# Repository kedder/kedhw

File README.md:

# Various electronics projects for gliding

This is a collection of various electronics projects, generally supposed to be used in
glider cockpit. Each directory here is a separate hardware design. See README in each of
the subdirectories for more info.

## [FLARM Splitter](flarmsplit)

FLARM splitter allows to connect both vario and FLARM viewer to the FLARM device via the
standard RJ45 socket, providing RS232 data. 

## [FLARM - USB adapter](flarmusb)

FLARM to USB adapter allows to connect flarm device to the computer for firmware update.
It also creates a virtual COM device in the computer OS allowing data communication with
the FLARM device.

## [TTLINK](ttlink)

USB adapter that allows to connect various loggers and handheld computers to the
Openvario via the USB interface. Compatible hardware list includes "LXNAV Nano 4" and
"Naviter Oudie", and possibly others.

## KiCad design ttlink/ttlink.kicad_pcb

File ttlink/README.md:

# USB-TTL Adapter

Simple USB adapter to connect devices like LXNAV Nano loggers or Oudie. Even
though these devices have a standard micro/mini USB sockets, they do not talk
USB protocol with glider electonics. Instead, they use TTL signal. This adapter
uses CH340G chip to convert USB protocol to TTL.

## Schematics

Current schematics can be also downloaded in
[PDF format](drawings/ttlink.pdf?raw=true).

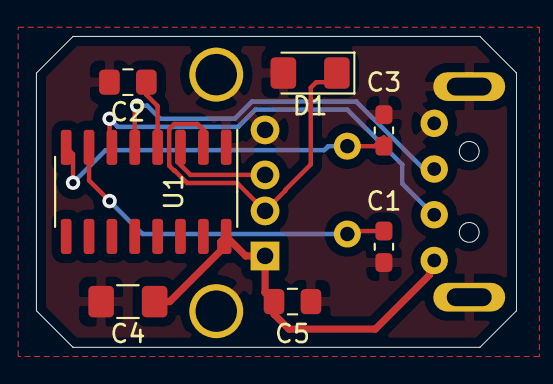
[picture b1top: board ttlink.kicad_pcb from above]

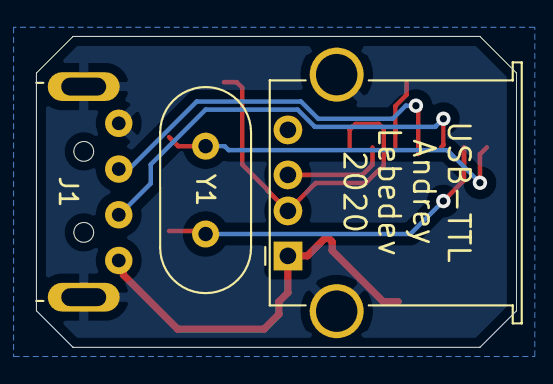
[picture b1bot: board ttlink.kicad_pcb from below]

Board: 2 copper layers, 26.7 x 17.3 mm, 10 parts (3 on the bottom side), 9 nets.

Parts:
C1, C3: 22pF; C_0603_1608Metric_Pad1.05x0.95mm_HandSolder
C2, C5: 0.1uF; C_0805_2012Metric_Pad1.15x1.40mm_HandSolder
C4: 10uF; C_1206_3216Metric_Pad1.42x1.75mm_HandSolder
D1: 1N4148; D_1206_3216Metric_Pad1.42x1.75mm_HandSolder
J1: USB; USB2_A_Plug_Horizontal
J2: TTL; USB_A_Stewart_SS-52100-001_Horizontal
U1: CH340G; SOIC-16_3.9x9.9mm_P1.27mm
Y1: 12MHz; Crystal_HC49-4H_Vertical

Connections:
+5V: C4.2, C5.2, J1.1, J2.1, U1.16
Earth: C1.2, C2.2, C3.2, C4.1, C5.1, D1.2, J1.4, J1.5, J2.4, J2.5, U1.1
unnamed: C1.1, U1.7, Y1.2
unnamed: C2.1, U1.4
unnamed: C3.1, U1.8, Y1.1
unnamed: D1.1, J2.2, U1.2
unnamed: J1.2, U1.6
unnamed: J1.3, U1.5
unnamed: J2.3, U1.3

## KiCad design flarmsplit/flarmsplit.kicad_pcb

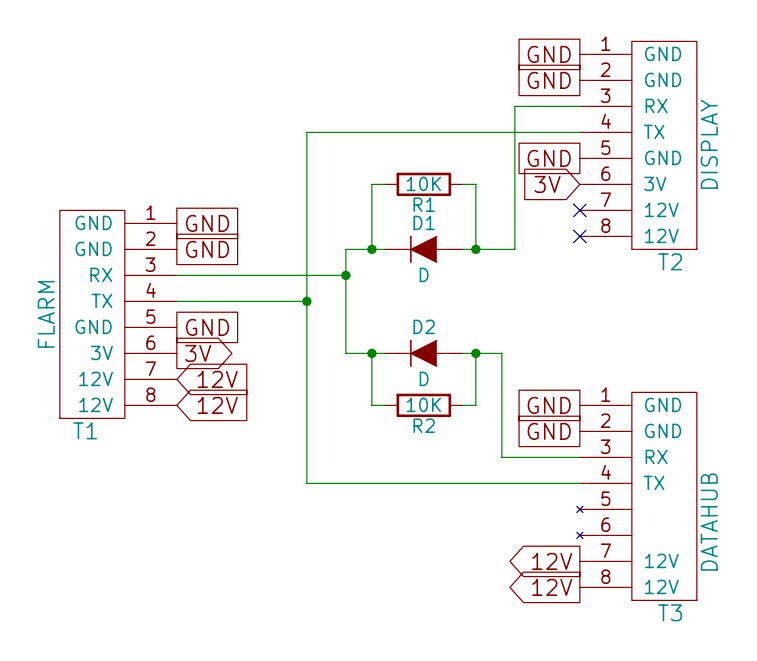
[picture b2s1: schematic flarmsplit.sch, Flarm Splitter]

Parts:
D1, D2: D; D_1206_3216Metric_Pad1.42x1.75mm_HandSolder
R1, R2: 10K; R_0805_2012Metric_Pad1.15x1.40mm_HandSolder
T1: FLARM; RJ45_SOCKET_SHLD
T2: DISPLAY; RJ45_SOCKET_SHLD
T3: DATAHUB; RJ45_SOCKET_SHLD

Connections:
3V: T1.6 (3V), T2.6 (3V)
12V: T1.7 (12V), T1.8 (12V), T3.7 (12V), T3.8 (12V)
GND: T1.1 (GND), T1.2 (GND), T1.5 (GND), T2.1 (GND), T2.2 (GND), T2.5 (GND), T3.1 (GND), T3.2 (GND)
unnamed: D1.1 (K), D2.1 (K), R1.2, R2.2, T1.3 (RX)
unnamed: D1.2 (A), R1.1, T2.3 (RX)
unnamed: D2.2 (A), R2.1, T3.3 (RX)
unnamed: T1.4 (TX), T2.4 (TX), T3.4 (TX)

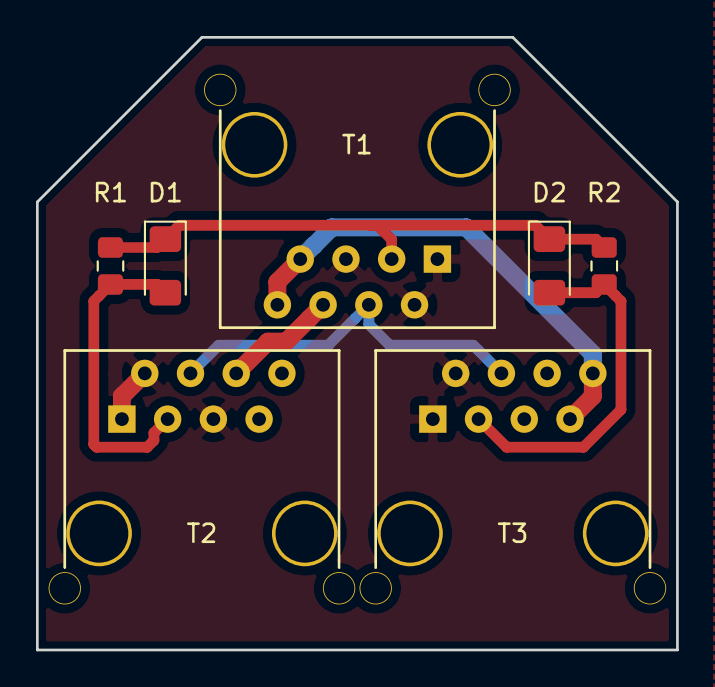
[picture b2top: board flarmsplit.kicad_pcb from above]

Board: 2 copper layers, 35.6 x 34.0 mm, 7 parts (0 on the bottom side), 7 nets.

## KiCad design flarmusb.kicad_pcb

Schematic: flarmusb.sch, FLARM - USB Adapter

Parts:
C1, C2: 22pF; C_0603_1608Metric
C3, C4, C5, C6, C7, C8: 100nF; C_0805_2012Metric
C9: 1uF; C_0805_2012Metric
C10: 47uF; C_0805_2012Metric
D1: SS14; D_SMA
D2: GREEN; LED_0603_1608Metric
D3: RED; LED_0603_1608Metric
J1: USB_B_Micro; USB_Micro
J2: Barrel_Jack_Switch; DC002
J3: RJ45_Shielded; RJ45_SOCKET_SHLD
R1, R2: 520R; R_0805_2012Metric
U1: LM3940-3.3; SOT-223-3_TabPin2
U2: CH340G; SOIC-16_3.9x9.9mm_P1.27mm
U3: MAX3232; SOIC-16_3.9x9.9mm_P1.27mm
Y1: 12M; Crystal_HC49-4H_Vertical

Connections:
3V3: C3.1, C5.2, C7.1, C10.2, R1.1, R2.1, U1.3, U2.4, U2.16, U3.16
/5V: C9.2, J1.1, U1.1
/12V: D1.1 (K), J3.7, J3.8
/12VR: D1.2 (A), J2.1
/RS232_RX: J3.4, U3.13
/RS232_TX: J3.3, U3.14
/TTL_RX: D2.1, U2.3, U3.12
/TTL_TX: D3.1, U2.2, U3.11
/USB_D+: J1.3, U2.5
/USB_D-: J1.2, U2.6
/USB_XI: C1.1, U2.7, Y1.1
Earth: C1.2, C2.2, C3.2, C5.1, C8.1, C9.1, C10.1, J1.4, J1.5, J1.6, J2.2, J2.3, J3.1, J3.2, J3.SH, U1.2, U2.1, U3.15
unnamed: C2.1, U2.8, Y1.2
unnamed: C4.1, U3.1
unnamed: C4.2, U3.3
unnamed: C6.1, U3.4
unnamed: C6.2, U3.5
unnamed: C7.2, U3.2
unnamed: C8.2, U3.6
unnamed: D2.2, R1.2
unnamed: D3.2, R2.2

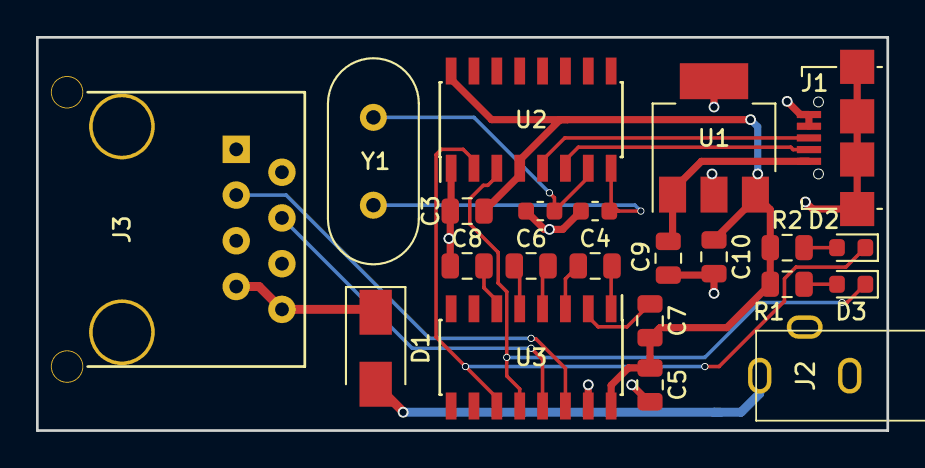
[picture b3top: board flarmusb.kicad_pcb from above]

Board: 2 copper layers, 47.2 x 21.8 mm, 22 parts (0 on the bottom side), 21 nets.

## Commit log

2019-10-15 PCB traced
2019-10-28 New footprint for DC002 connector
2019-10-28 DC002 connector drawings added
2019-10-28 Ignore backup files
2019-10-28 README added
2019-10-28 PCB silkscreen labels adjusted
2019-11-12 Prepare for production
2020-08-30 Move flarmusb project to the dedicated dir
2020-08-30 Add ttlink project
2020-08-30 Add flarmsplit project
2020-08-30 Ignore tmp dirs
2020-08-30 Add summary README
2020-08-30 Make link a relative one
2020-08-31 PCB layed out
2020-09-16 Footprint for usb plug
2020-09-16 Final PCB layout
2020-09-17 Final touches before submiting to production
2020-09-25 Set up drawing page
2020-09-25 Add schematic PDF
2020-09-26 Add readme for ttlink
